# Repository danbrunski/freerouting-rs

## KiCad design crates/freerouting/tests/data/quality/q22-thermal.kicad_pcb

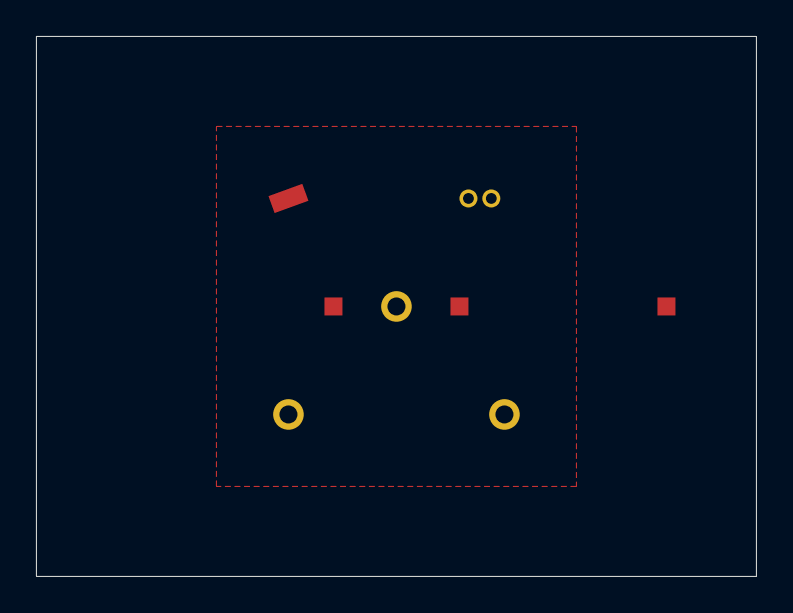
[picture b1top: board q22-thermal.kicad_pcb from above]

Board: 2 copper layers, 40.0 x 30.0 mm, 8 parts (0 on the bottom side), 2 nets, no tracks yet.

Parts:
J1: x; pth
P2: x; pad
PA1, PA2: x; pad
U2: x; rect
U3, U4: x; pth
U5: x; pitch127

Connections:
A: PA1.1, PA2.1, U5.2
GND: J1.1, P2.1, U2.1, U3.1, U4.1, U5.1

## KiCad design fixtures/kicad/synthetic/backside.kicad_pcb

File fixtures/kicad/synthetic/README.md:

# Synthetic boards (K05.8)

Generated once with pcbnew (KiCad 10.0.7, Ubuntu package, WSL) by
`tools/kicad-reader/synthetic.py`; the exports `*.kicad10.dsn` come from
`tools/kicad-reader/export.sh` on the same KiCad. Not from the Java repository,
so they are not in `MANIFEST.tsv`. The board files hold random UUIDs: re-running
the script gives different files, so they are committed, not regenerated.

| Board | Covers |
|---|---|
| `pads` | one pad of each shape (circle, rect, oval, trapezoid, round rect, chamfered rect, custom with two primitives), rotated 0/30/90 degrees by three footprint rotations, a pad offset, an NPTH hole, a repeated pad number |
| `outline` | a concave notched outline with an arc, and a slot (inner contour) |
| `backside` | back-side parts at 0, 30, 90 and 225 degrees and front parts at 30 and 225 |
| `classes` | project schema 5: a wildcard pattern, an explicit assignment, a regular expression and a net matching two classes |
| `classes6` | project schema 2 (KiCad 6): a class's `nets` list, an explicit assignment |
| `rule-areas` (K06) | 4 layers: 13 board rule areas (tracks and vias, vias only, tracks only, footprints only, pads only, copper pour only, placement only, tracks and footprints, pads and footprints, `*.Cu`, `F&B.Cu`, one with a hole, inner layers), four copper zones (one with a hole, two netless on inner layers), six footprints that own rule areas at 0/30/135 degrees on both sides, and a footprint that owns a copper zone |
| `arcs` (K06) | 2 layers: a segment, an arc and a segment at radii 0.1, 1, 5 and 20 mm with sweeps of 10, 90, 270 and -90 degrees, and a locked segment |
| `vias` (K06) | 6 layers: a through via, blind (from the top and from the bottom), buried and micro vias, a locked via and two vias that share a padstack |

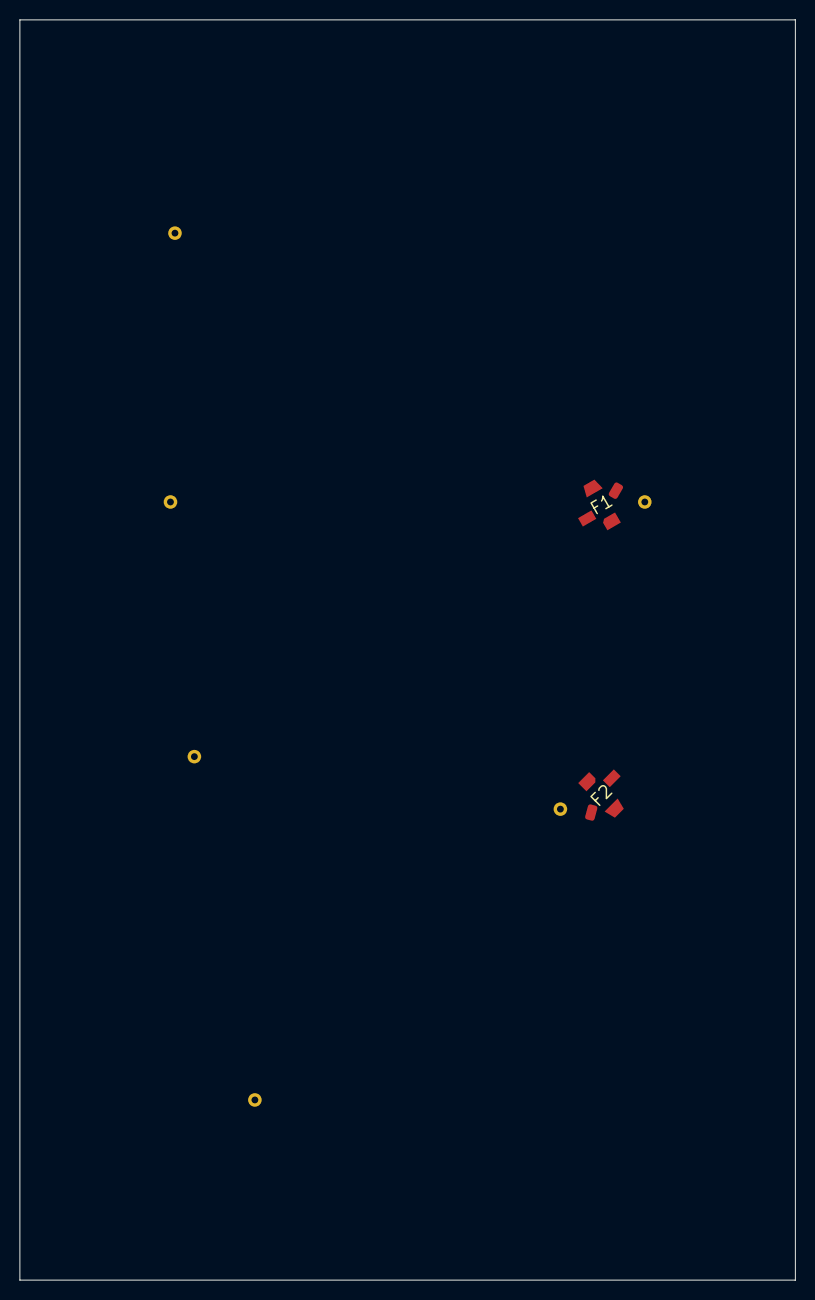
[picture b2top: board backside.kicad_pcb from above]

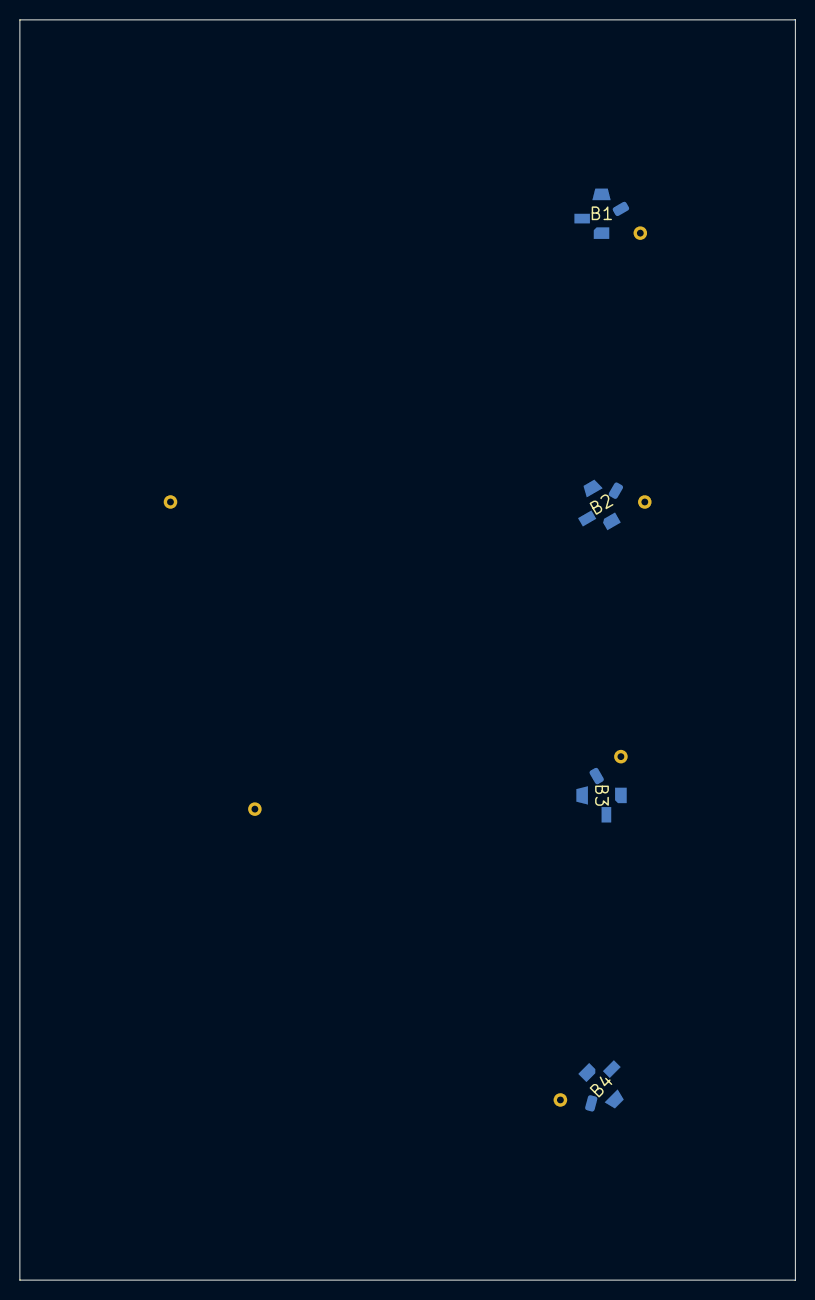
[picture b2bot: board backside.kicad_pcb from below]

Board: 4 copper layers, 80.0 x 130.0 mm, 6 parts (4 on the bottom side), 2 nets, no tracks yet.

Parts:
B1, B2, B3, B4: part; Part
F1, F2: part; Part

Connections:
N1: B1.1, B1.3, B1.5, B2.1, B2.3, B2.5, B3.1, B3.3, B3.5, B4.1, B4.3, B4.5, F1.1, F1.3, F1.5, F2.1, F2.3, F2.5
N2: B1.2, B1.4, B2.2, B2.4, B3.2, B3.4, B4.2, B4.4, F1.2, F1.4, F2.2, F2.4
